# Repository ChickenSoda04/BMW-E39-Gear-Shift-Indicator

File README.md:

# BMW E39 Gear Shift Indicator

A custom PCB gear shift indicator for the BMW E39, built from scratch — from a breadboard prototype and Arduino code, through a cardboard fitment mockup, a KiCad schematic/PCB, JLCPCB manufacturing, to a working install in the car.

## Table of Contents
- [1. Breadboard Prototype & Arduino Code](#1-breadboard-prototype--arduino-code)
- [2. Measuring Template with Cardboard](#2-measuring-template-with-cardboard)
- [3. KiCad Schematic & PCB](#3-kicad-schematic--pcb)
- [4. Printing from JLCPCB](#4-printing-from-jlcpcb)
- [5. Testing Assembly in Car](#5-testing-assembly-in-car)
- [6. Final Project Demo](#6-final-project-demo)
- [Credit](#credit)

---

## 1. Breadboard Prototype & Arduino Code

Before designing a PCB, I built the circuit on a breadboard — wiring up the display and hall effect sensors to an Arduino — and wrote and tested the code to make sure the logic and display output worked correctly before committing to a custom board. The display datasheets were extremely helpful for getting the screen working with the Arduino micro controller. 

**Initial screen demo:**
<p align="center">
  <video src="https://github.com/user-attachments/assets/d19b766d-0b28-46d4-b545-26aa207e68b7" controls width="600">
    Your browser does not support the video tag.
  </video>
</p>

<p align="center">
  <video src="https://github.com/user-attachments/assets/6b89061c-957d-4a28-bf3f-c886c59b977f" controls width="600">
    Your browser does not support the video tag.
  </video>
</p>

---

## 2. Measuring Template with Cardboard

Before committing to a PCB outline, I cut a cardboard template to match the exact mounting space in the dash/console, so the final board would drop in without any fitment surprises.

<p align="center">
  <video src="https://raw.githubusercontent.com/ChickenSoda04/BMW-E39-Gear-Shift-Indicator/main/videos/cardboard_template.mp4" controls width="600">
    Your browser does not support the video tag.
  </video>
</p>

---

## 3. KiCad Schematic & PCB

With the form factor confirmed, I designed the schematic and PCB layout in KiCad, matching the board outline to the cardboard template.

**Schematic:**

**PCB Layout (Front / Back):**

**3D render walkthrough:**
<p align="center">
  <video src="https://github.com/user-attachments/assets/9900a72d-7016-4ad4-b393-e1eb116858c7
" controls width="600">
    Your browser does not support the video tag.
  </video>
</p>

All CAD source files (schematic, PCB, project, and Gerbers) are in [`gear_indicator_cad_files/`](gear_indicator_cad_files).

---

## 4. Printing from JLCPCB

Once the design was finalized, the Gerber files were sent to JLCPCB for manufacturing.

<p align="center">
  <video src="https://raw.githubusercontent.com/ChickenSoda04/BMW-E39-Gear-Shift-Indicator/main/videos/printed_pcb.mp4" controls width="600">
    Your browser does not support the video tag.
  </video>
</p>

---

## 5. Testing Assembly in Car

With the printed board in hand, next came test-fitting it in the car and validating the hall effect sensors against actual gear shift positions.

**Fitment test:**
<p align="center">
  <video src="https://github.com/user-attachments/assets/2465236a-05b8-4c8a-bc68-1f0bb54ee02c" controls width="600">
    Your browser does not support the video tag.
  </video>
</p>

---

## 6. Final Project Demo

The finished gear shift indicator, installed and running in the car.

<p align="center">
  <video src="https://github.com/user-attachments/assets/e65f4005-9a61-41ae-bb93-482aaea8f4e5
" controls width="600">
    Your browser does not support the video tag.
  </video>
</p>

---

## Credit

The round IPS display wiring, driver setup, and screen graphics approach used in this project were based on [upir](https://www.youtube.com/@upir_upir)'s tutorial, [Arduino UNO with Round LCD IPS Display](https://www.youtube.com/watch?v=pbqgrv5YSf0&list=PLYljjO3cgruen1KPtTqZPnxCy7SrkpltR&index=12). Big thanks for the clear breakdown of the display setup and code.

**Display datasheets / reference docs:**
- [MSP0962/MSP0963 Specification (PDF)](https://www.lcdwiki.com/res/MSP0962_MSP0963/MSP0962_MSP0963_Specification_EN_V1.0.pdf)
- [MSP0962/MSP0963 SPI Demo Instructions — UNO/Mega2560 (PDF)](https://www.lcdwiki.com/res/MSP0962_MSP0963/0.96inch_SPI_MSP0962_MSP0963_UNO_Mega2560_Demo_Instructions_EN.pdf)

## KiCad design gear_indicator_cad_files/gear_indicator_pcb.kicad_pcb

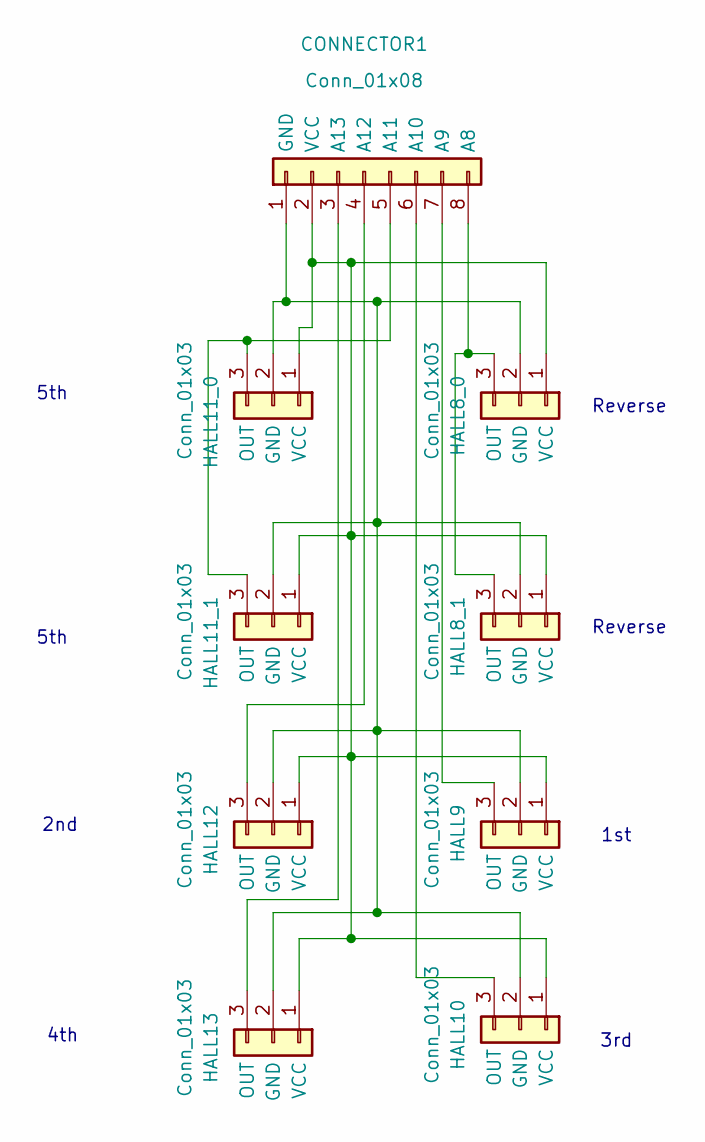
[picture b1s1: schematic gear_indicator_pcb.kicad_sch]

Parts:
CONNECTOR1: Conn_01x08; PinHeader_1x08_P2.54mm_Vertical
HALL8_0, HALL8_1, HALL9, HALL10, HALL11_0, HALL11_1, HALL12, HALL13: Conn_01x03; PinHeader_1x03_P2.54mm_Vertical

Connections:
unnamed: CONNECTOR1.8 (A8), HALL8_0.3 (OUT), HALL8_1.3 (OUT)
unnamed: CONNECTOR1.7 (A9), HALL9.3 (OUT)
unnamed: CONNECTOR1.6 (A10), HALL10.3 (OUT)
unnamed: CONNECTOR1.5 (A11), HALL11_0.3 (OUT), HALL11_1.3 (OUT)
unnamed: CONNECTOR1.4 (A12), HALL12.3 (OUT)
unnamed: CONNECTOR1.3 (A13), HALL13.3 (OUT)
unnamed: CONNECTOR1.1 (GND), HALL8_0.2 (GND), HALL8_1.2 (GND), HALL9.2 (GND), HALL10.2 (GND), HALL11_0.2 (GND), HALL11_1.2 (GND), HALL12.2 (GND), HALL13.2 (GND)
unnamed: CONNECTOR1.2 (VCC), HALL8_0.1 (VCC), HALL8_1.1 (VCC), HALL9.1 (VCC), HALL10.1 (VCC), HALL11_0.1 (VCC), HALL11_1.1 (VCC), HALL12.1 (VCC), HALL13.1 (VCC)

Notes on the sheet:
1st
5th
2nd
Reverse
3rd
4th
Reverse

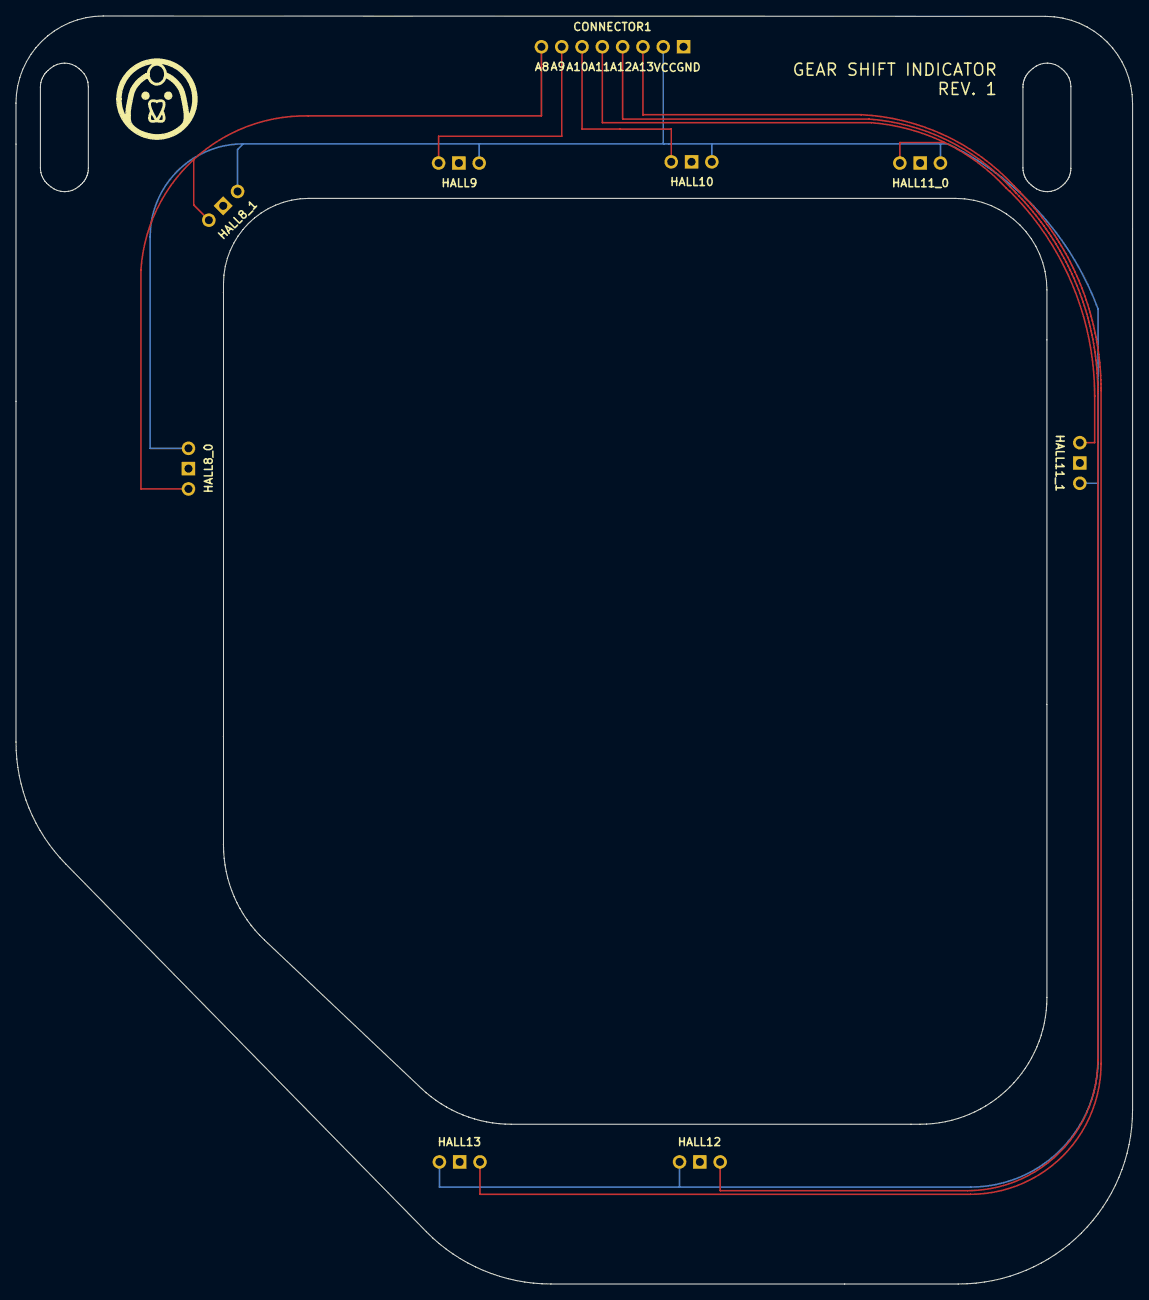
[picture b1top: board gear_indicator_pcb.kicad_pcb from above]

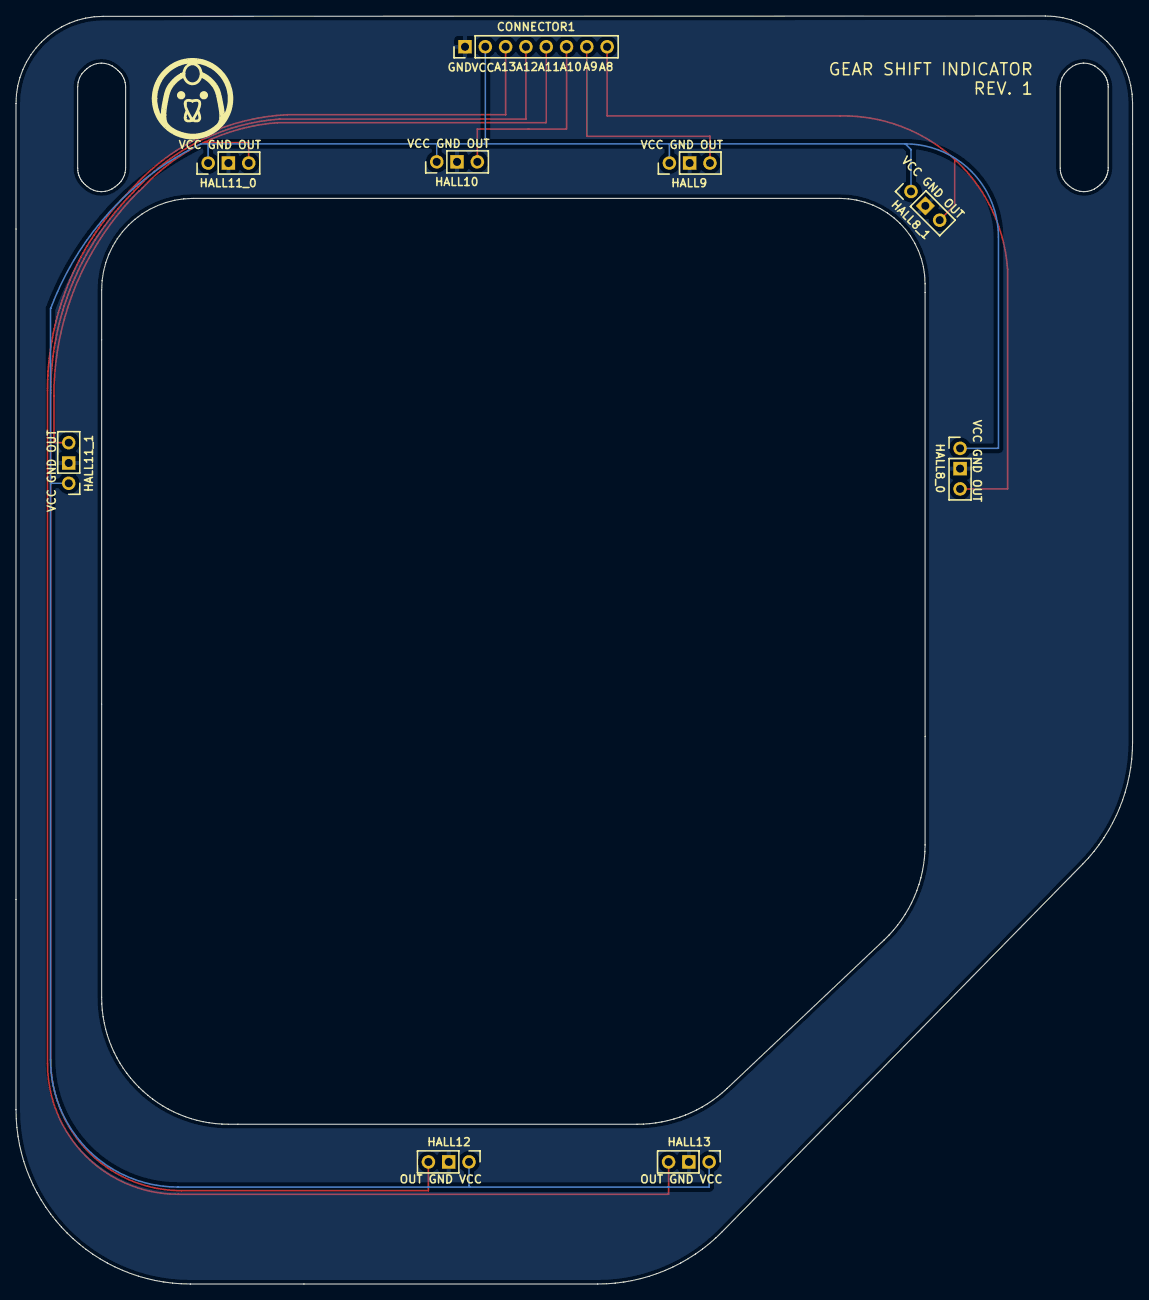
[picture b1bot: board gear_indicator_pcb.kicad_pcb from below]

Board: 2 copper layers, 139.7 x 158.7 mm, 9 parts (9 on the bottom side), 8 nets.
